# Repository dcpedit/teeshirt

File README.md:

# TeeShirt Keyboard

TeeShirt is a ergonomic monoblock keyboard with a one-size-fits-some PCB design that supports 3 different sized builds: S, M, and L.

## Features

* [Size S](https://github.com/dcpedit/teeshirt/tree/master/small-build): case-less barebones keyboard build
* [Size M](https://github.com/dcpedit/teeshirt/tree/master/medium-build): custom slim acrylic case build
* [Size L](https://github.com/dcpedit/teeshirt/tree/master/large-build): standard 60% case (GH60 compatible) build
* Supports 1.5u and 1.25u thumb keys to reduce gap between keycaps
* Spacebars can be 2u or 1.5u for stab-less builds
* Center key can be swapped out for a rotary encoder
* Supports 128x32 OLED display
* Utilizes hot swap sockets
* Uses ProMicro MCU footprint: Elite-C, Nice!Nano, etc.

## Sponsors

The first revision of the PCB was sponsored by PCBWay, so a huge thanks to them for helping get this project off the ground.  Their KiCad plugin made it super easy to send the design directly to their site, where you can place the order and have it shipped out with just a few clicks.

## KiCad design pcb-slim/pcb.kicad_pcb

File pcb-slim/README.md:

# TeeShirt PCB

The PCB automatically applies power to the VBUS pin, but if you want to also send power to the RAW pin (#24), you can short JP1.

If you're relocating the USB port to the upper left of the PCB for the large sized (60%) builds, make sure you also soldering in 5.1k resistors, as well as connecting the data pins on the PCB (D+/D-) to the data pins/pads to the MCU with wires.

For the small builds, the MCU can be mounted on the top side with headers.

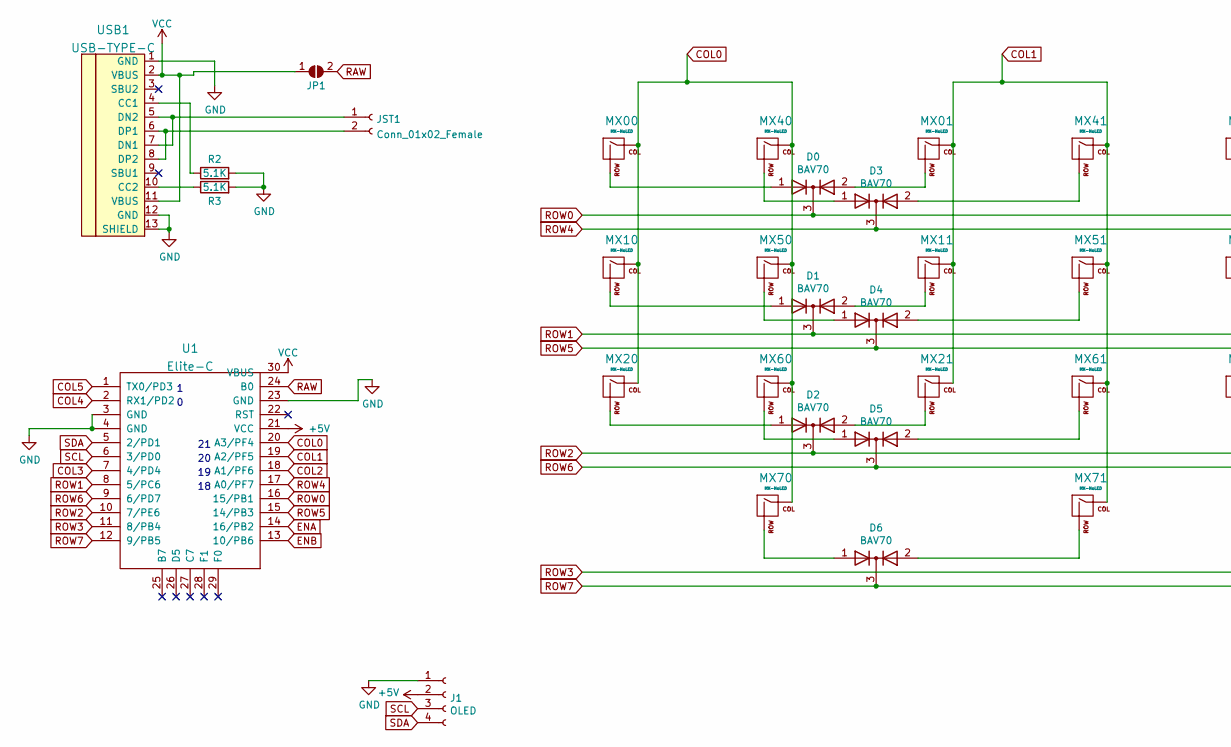
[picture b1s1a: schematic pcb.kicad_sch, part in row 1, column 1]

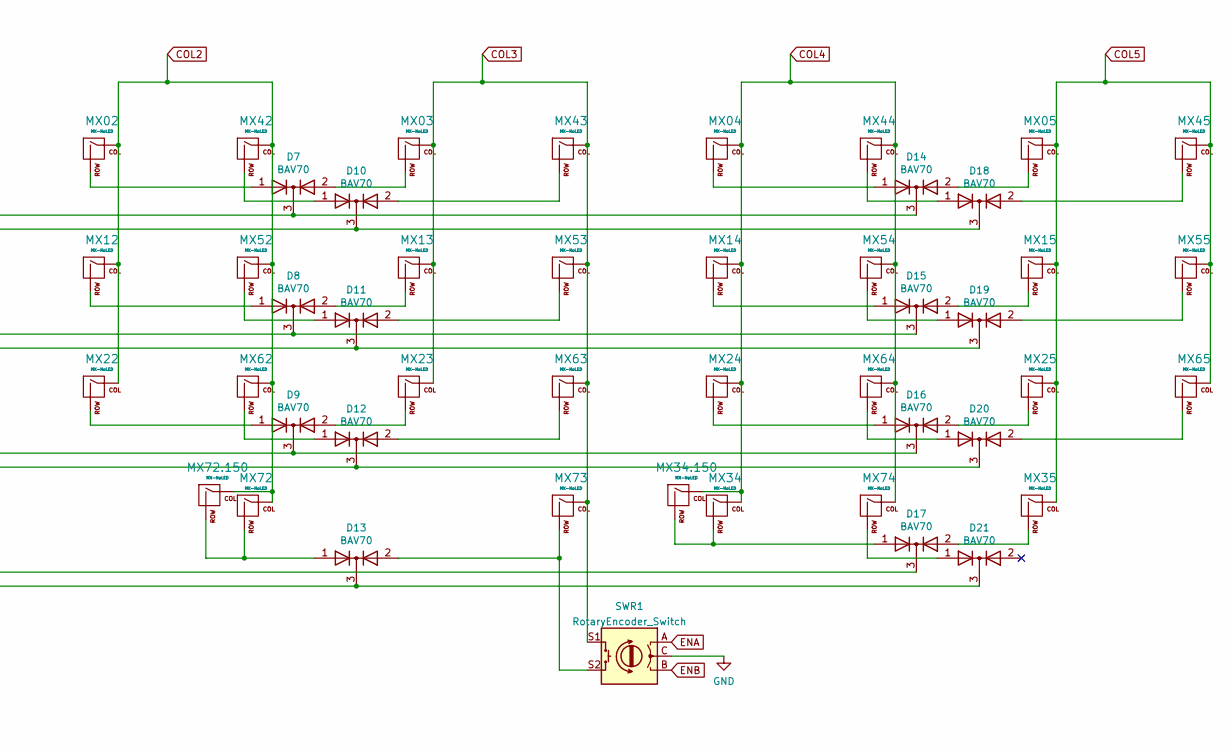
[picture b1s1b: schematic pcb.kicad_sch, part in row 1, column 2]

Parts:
D0, D1, D2, D3, D4, D5, D6, D7, D8, D9, D10, D11, D12, D13, D14, D15, D16, D17, D18, D19, D20, D21: BAV70; SOT-23_Handsoldering
J1: OLED; SSD1306_OLED
JP1: SolderJumper_2_Open; SolderJumper-2_P1.3mm_Open_RoundedPad1.0x1.5mm
JST1: Conn_01x02_Female
MX00, MX01, MX02, MX03, MX04, MX05, MX10, MX11, MX12, MX13, MX14, MX15, MX20, MX21, MX22, MX23, MX24, MX25, MX34, MX34.150, MX35, MX40, MX41, MX42, MX43, MX44, MX45, MX50, MX51, MX52, MX53, MX54, MX55, MX60, MX61, MX62, MX63, MX64, MX65, MX70, MX71, MX72, MX72.150, MX73, MX74: MX-NoLED; MXOnly-1U-NoLED
R2, R3: 5.1K; R_0805_2012Metric_Pad1.20x1.40mm_HandSolder; LCSC C27834
SWR1: RotaryEncoder_Switch
U1: Elite-C
USB1: USB-TYPE-C

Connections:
+5V: J1.2, U1.21 (VCC)
COL0: MX00.1 (COL), MX10.1 (COL), MX20.1 (COL), MX40.1 (COL), MX50.1 (COL), MX60.1 (COL), MX70.1 (COL), U1.20 (A3/PF4)
COL1: MX01.1 (COL), MX11.1 (COL), MX21.1 (COL), MX41.1 (COL), MX51.1 (COL), MX61.1 (COL), MX71.1 (COL), U1.19 (A2/PF5)
COL2: MX02.1 (COL), MX12.1 (COL), MX22.1 (COL), MX42.1 (COL), MX52.1 (COL), MX62.1 (COL), MX72.1 (COL), MX72.150.1 (COL), U1.18 (A1/PF6)
COL3: MX03.1 (COL), MX13.1 (COL), MX23.1 (COL), MX43.1 (COL), MX53.1 (COL), MX63.1 (COL), MX73.1 (COL), SWR1.S1, U1.7 (4/PD4)
COL4: MX04.1 (COL), MX14.1 (COL), MX24.1 (COL), MX34.1 (COL), MX34.150.1 (COL), MX44.1 (COL), MX54.1 (COL), MX64.1 (COL), MX74.1 (COL), U1.2 (RX1/PD2)
COL5: MX05.1 (COL), MX15.1 (COL), MX25.1 (COL), MX35.1 (COL), MX45.1 (COL), MX55.1 (COL), MX65.1 (COL), U1.1 (TX0/PD3)
ENA: SWR1.A, U1.14 (16/PB2)
ENB: SWR1.B, U1.13 (10/PB6)
GND: J1.1, R2.2, R3.2, SWR1.C, U1.3 (GND), U1.4 (GND), U1.23 (GND), USB1.1 (GND), USB1.12 (GND), USB1.13 (SHIELD)
unnamed: D0.1 (A), MX00.2 (ROW)
unnamed: D0.2 (A), MX01.2 (ROW)
unnamed: D1.1 (A), MX10.2 (ROW)
unnamed: D1.2 (A), MX11.2 (ROW)
unnamed: D2.1 (A), MX20.2 (ROW)
unnamed: D2.2 (A), MX21.2 (ROW)
unnamed: D3.1 (A), MX40.2 (ROW)
unnamed: D3.2 (A), MX41.2 (ROW)
unnamed: D4.1 (A), MX50.2 (ROW)
unnamed: D4.2 (A), MX51.2 (ROW)
unnamed: D5.1 (A), MX60.2 (ROW)
unnamed: D5.2 (A), MX61.2 (ROW)
unnamed: D6.1 (A), MX70.2 (ROW)
unnamed: D6.2 (A), MX71.2 (ROW)
unnamed: D7.1 (A), MX02.2 (ROW)
unnamed: D7.2 (A), MX03.2 (ROW)
unnamed: D8.1 (A), MX12.2 (ROW)
unnamed: D8.2 (A), MX13.2 (ROW)
unnamed: D9.1 (A), MX22.2 (ROW)
unnamed: D9.2 (A), MX23.2 (ROW)
unnamed: D10.1 (A), MX42.2 (ROW)
unnamed: D10.2 (A), MX43.2 (ROW)
unnamed: D11.1 (A), MX52.2 (ROW)
unnamed: D11.2 (A), MX53.2 (ROW)
unnamed: D12.1 (A), MX62.2 (ROW)
unnamed: D12.2 (A), MX63.2 (ROW)
unnamed: D13.1 (A), MX72.2 (ROW), MX72.150.2 (ROW)
unnamed: D13.2 (A), MX73.2 (ROW), SWR1.S2
unnamed: D14.1 (A), MX04.2 (ROW)
unnamed: D14.2 (A), MX05.2 (ROW)
unnamed: D15.1 (A), MX14.2 (ROW)
unnamed: D15.2 (A), MX15.2 (ROW)
unnamed: D16.1 (A), MX24.2 (ROW)
unnamed: D16.2 (A), MX25.2 (ROW)
unnamed: D17.1 (A), MX34.2 (ROW), MX34.150.2 (ROW)
unnamed: D17.2 (A), MX35.2 (ROW)
unnamed: D18.1 (A), MX44.2 (ROW)
unnamed: D18.2 (A), MX45.2 (ROW)
unnamed: D19.1 (A), MX54.2 (ROW)
unnamed: D19.2 (A), MX55.2 (ROW)
unnamed: D20.1 (A), MX64.2 (ROW)
unnamed: D20.2 (A), MX65.2 (ROW)
unnamed: D21.1 (A), MX74.2 (ROW)
unnamed: R2.1, USB1.4 (CC1)
unnamed: R3.1, USB1.10 (CC2)
unnamed: JST1.1, USB1.5 (DN2), USB1.7 (DN1)
unnamed: JST1.2, USB1.6 (DP1), USB1.8 (DP2)
RAW: JP1.2 (B), U1.24 (B0)
ROW0: D0.3 (K), D7.3 (K), D14.3 (K), U1.16 (15/PB1)
ROW1: D1.3 (K), D8.3 (K), D15.3 (K), U1.8 (5/PC6)
ROW2: D2.3 (K), D9.3 (K), D16.3 (K), U1.10 (7/PE6)
ROW3: D17.3 (K), U1.11 (8/PB4)
ROW4: D3.3 (K), D10.3 (K), D18.3 (K), U1.17 (A0/PF7)
ROW5: D4.3 (K), D11.3 (K), D19.3 (K), U1.15 (14/PB3)
ROW6: D5.3 (K), D12.3 (K), D20.3 (K), U1.9 (6/PD7)
ROW7: D6.3 (K), D13.3 (K), D21.3 (K), U1.12 (9/PB5)
SCL: J1.3, U1.6 (3/PD0)
SDA: J1.4, U1.5 (2/PD1)
VCC: JP1.1 (A), U1.30 (VBUS), USB1.2 (VBUS), USB1.11 (VBUS)

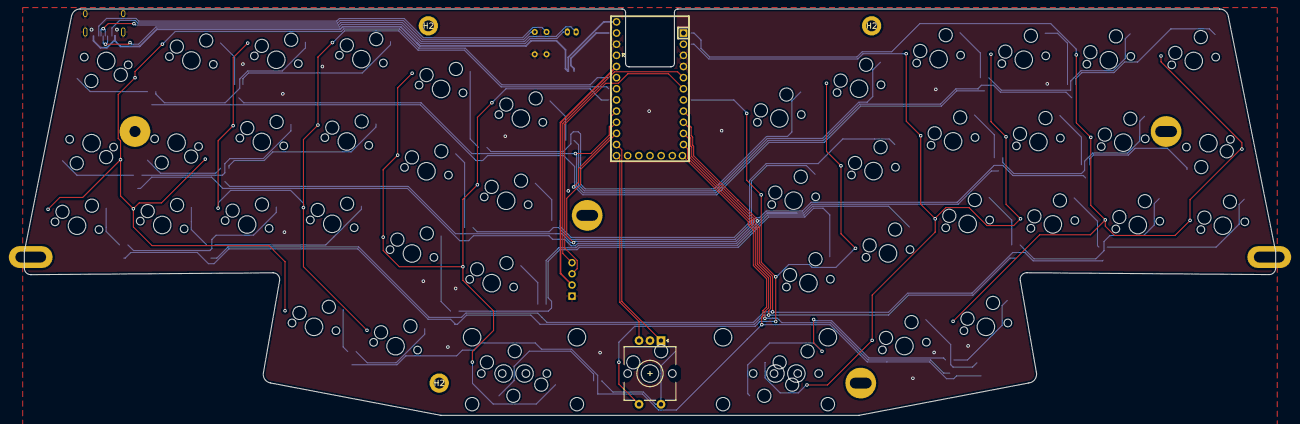
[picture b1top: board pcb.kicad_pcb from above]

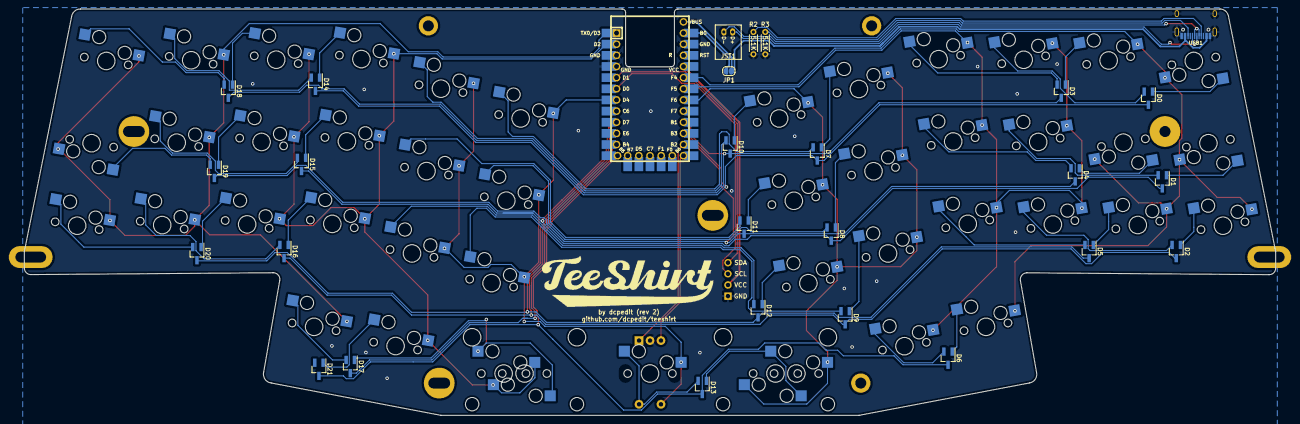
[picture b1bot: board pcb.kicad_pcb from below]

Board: 2 copper layers, 285.0 x 92.5 mm, 84 parts (28 on the bottom side), 69 nets.

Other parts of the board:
H2, H2#2, H2#3: (no value)
HOLE: VAL**; PKRH
HOLE#2, HOLE#4: VAL**; PKRH
HOLE#3, HOLE#5: VAL**; PKRHSL
HOLE#6: VAL**; PKRHC

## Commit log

2022-10-01 Case updates
2022-11-11 Manual and bare case files
2022-11-26 Add readme
2022-11-26 Add full pcb readme
2022-11-26 Remove experimental files
2022-11-29 Add readme files and rename folders
2022-11-29 upate readme
2022-11-30 Add PCB readme
2022-11-30 Readme updates
2022-12-01 Add gerbers
2022-12-01 Export to DXF
2022-12-04 Add USB port to guide
2022-12-24 Plover HID readme
2022-12-24 Move files
2022-12-24 Update firmware path
2022-12-25 Add build notes to plover readme
2023-03-07 Add notes from trogdoro
2023-03-07 Add screenshot
2023-03-07 Add note about reconnect plugin
2023-11-03 Update README.md github link
